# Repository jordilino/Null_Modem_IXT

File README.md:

# Null Modem IXT

`Null_Modem_IXT` is an open-source hardware board designed for RS-232 serial communication switching and signal monitoring. It allows users to toggle between a direct pass-through connection and a Null Modem cross-over configuration using a high-durability DIP switch, featuring dedicated test points for oscilloscope grounding and lab instrumentation.

## Hardware Overview

| Front View | Back View | Lab Test Setup |
| :---: | :---: | :---: |
|  |  |  |

---

## Technical Specifications
* **PCB Dimensions**: 70.01 mm × 51.96 mm
* **Design Software**: KiCad 9.0.3
* **Layer Count**: 2-layer THT design (Top Copper / Bottom Copper)
* **Primary Connectors**: 2× DB9 Female Right-Angle (90°) THT connectors with UNC 4-40 jack screws
* **DIP Switch**: Omron A6T Series (or equivalent) rated for $\ge 1,000$ operations min.
* **Ground Reference**: 
  * 1×4 mm Banana Socket / Test Point for lab power supply or chassis ground

---

## Repository Structure
```text
Null_Modem_IXT/
├── LICENSE_HARDWARE            # CERN-OHL-S-v2 License
├── LICENSE_DOCUMENTATION       # CC-BY-SA 4.0 License
├── README.md                   # Main English documentation
├── README_CA.md                # Catalan documentation
├── img/                        # Project photos & test setups
│   ├── Null_Modem_IXT_Front.png
│   ├── Null_Modem_IXT_Back.png
│   └── Null_Modem_IXT_Test.png
├── hardware/                  # KiCad source design files
│   ├── Null_Modem_IXT.kicad_pro
│   ├── Null_Modem_IXT.kicad_sch
│   ├── Null_Modem_IXT.kicad_pcb
│   └── Null_Modem_IXT.kicad_dru
├── production/                # Manufacturing deliverables
│   ├── gerbers/               # Gerber RS-274X files
│   │   ├── Null_Modem_IXT-F_Cu.gbr
│   │   ├── Null_Modem_IXT-B_Cu.gbr
│   │   ├── Null_Modem_IXT-F_Mask.gbr
│   │   ├── Null_Modem_IXT-B_Mask.gbr
│   │   ├── Null_Modem_IXT-F_Silkscreen.gbr
│   │   ├── Null_Modem_IXT-Edge_Cuts.gbr
│   │   └── Null_Modem_IXT.drl
│   ├── Null_Modem_IXT_BOM.csv
│   └── Null_Modem_IXT_Schematic.pdf
```
---

## Bill of Materials (BOM)
| Reference | Qty | Value / Component | Package / Footprint | Description / Part Number |
| :--- | :--- | :--- | :--- | :--- |
| J1, J2 | 2 | DB9 Female 90° | DB9_Female_RightAngle_THT | RS-232 Female Connector, 90° PCB Mount |
| InterruptorAtoB1 | 1 | Omron A6T DIP Switch | DIP-12 Slide Switch | 12-Position DIP Switch ($\ge 1,000$ cycles) |
| PINFEMELLA(a)1, PINFEMELLA(b)1 | 2 | Female Pin Header 12x1 | PinHeader_1x12_P2.54mm_Vertical | Breakout / Break-in test headers |
| GND(banana)1 | 1 | 4mm Banana Socket | Socket_Banana_4mm_THT | Lab Ground Binding Post |
| GND_Turret | 1 | Mechanical Turret Terminal | Terminal_Turret_THT | Oscilloscope Ground Probe Attachment Post |

---

## Open Source Hardware Compliance & Licensing

This project fully complies with the [OSHWA Open Source Hardware Definition](https://www.oshwa.org/definition/).

### License Terms
* **Hardware Design** (Schematics, PCB layout, Gerbers): Licensed under the **CERN Open Hardware Licence Strongly Reciprocal v2** ([CERN-OHL-S-v2](https://ohwr.org/cern_ohl_s_v2.txt)).
* **Documentation & Media**: Licensed under the **Creative Commons Attribution-ShareAlike 4.0 International License** ([CC-BY-SA 4.0](https://creativecommons.org/licenses/by-sa/4.0/)).

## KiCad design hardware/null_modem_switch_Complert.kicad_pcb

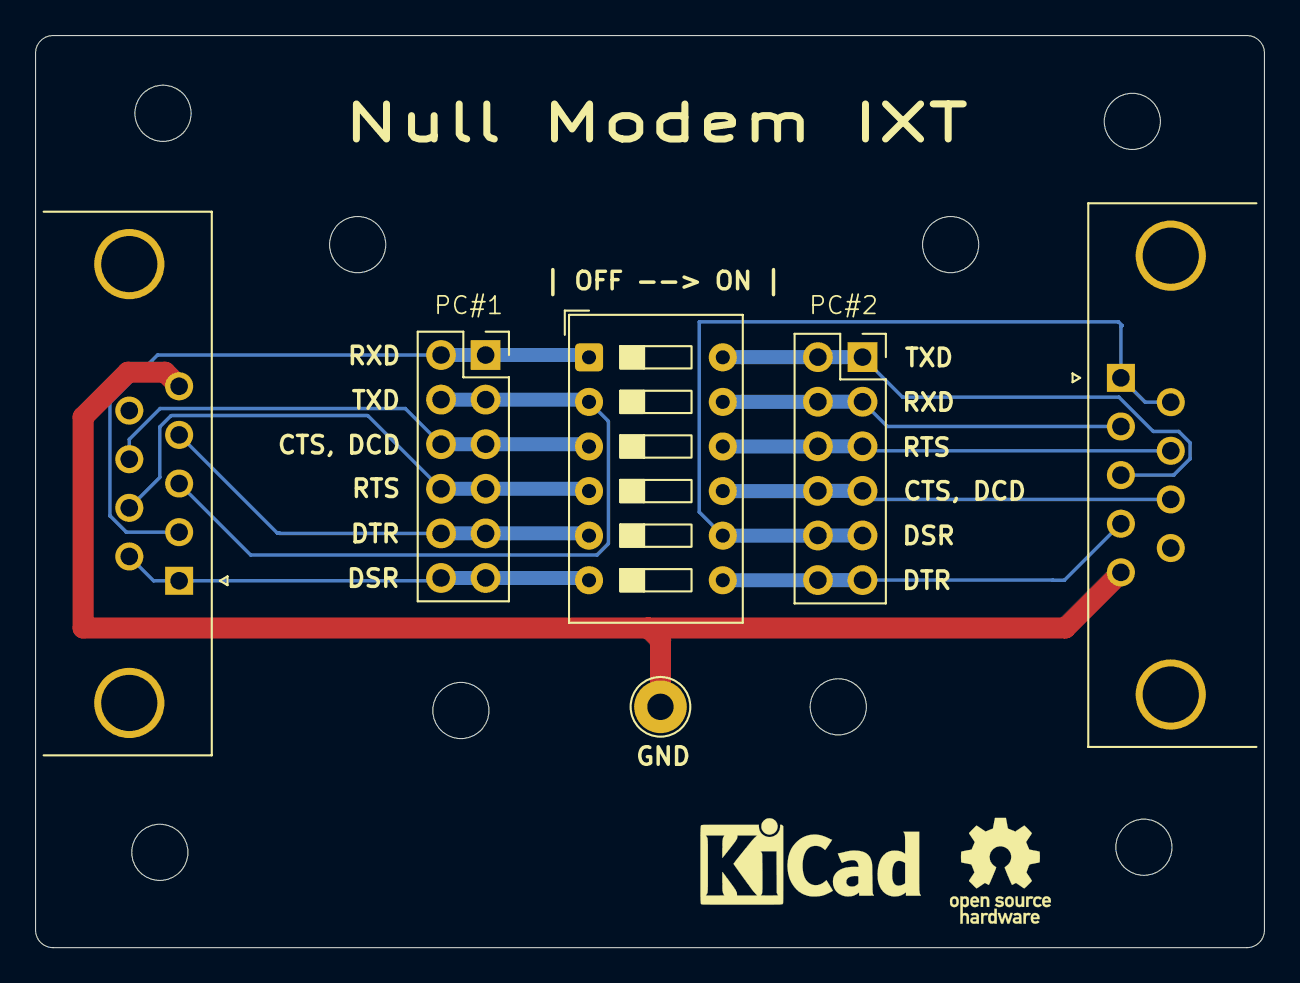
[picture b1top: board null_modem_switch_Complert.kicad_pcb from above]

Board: 2 copper layers, 70.0 x 52.0 mm, 6 parts (0 on the bottom side), 13 nets.

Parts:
GND(banana)1: Terra; TestPoint_Loop_D2.54mm_Drill1.5mm_Beaded
InterruptorAtoB1: A to B; SW_DIP_SPSTx06_Slide_9.78x17.42mm_W7.62mm_P2.54mm
J1, J2: DE9_Socket; DSUB-9_Socket_Horizontal_P2.77x2.84mm_EdgePinOffset4.94mm_H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
PINFEMELLA(a)1: Conn_02x06_Odd_Even; PinSocket_2x06_P2.54mm_Vertical
PINFEMELLA(b)1: Conn_02x06_Odd_Even; PinSocket_2x06_P2.54mm_Vertical

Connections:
unnamed: GND(banana)1.1, J1.5, J2.5
unnamed: InterruptorAtoB1.1, J2.2, PINFEMELLA(a)1.1, PINFEMELLA(a)1.2
unnamed: InterruptorAtoB1.2, J2.3, PINFEMELLA(a)1.3, PINFEMELLA(a)1.4
unnamed: InterruptorAtoB1.3, J2.8, PINFEMELLA(a)1.5, PINFEMELLA(a)1.6
unnamed: InterruptorAtoB1.4, J2.7, PINFEMELLA(a)1.7, PINFEMELLA(a)1.8
unnamed: InterruptorAtoB1.5, J2.4, PINFEMELLA(a)1.9, PINFEMELLA(a)1.10
unnamed: InterruptorAtoB1.6, J2.1, J2.6, PINFEMELLA(a)1.11, PINFEMELLA(a)1.12
unnamed: InterruptorAtoB1.12, J1.3, PINFEMELLA(b)1.1, PINFEMELLA(b)1.2
unnamed: InterruptorAtoB1.11, J1.2, PINFEMELLA(b)1.3, PINFEMELLA(b)1.4
unnamed: InterruptorAtoB1.10, J1.7, PINFEMELLA(b)1.5, PINFEMELLA(b)1.6
unnamed: InterruptorAtoB1.9, J1.8, PINFEMELLA(b)1.7, PINFEMELLA(b)1.8
unnamed: InterruptorAtoB1.8, J1.1, J1.6, PINFEMELLA(b)1.9, PINFEMELLA(b)1.10
unnamed: InterruptorAtoB1.7, J1.4, PINFEMELLA(b)1.11, PINFEMELLA(b)1.12
